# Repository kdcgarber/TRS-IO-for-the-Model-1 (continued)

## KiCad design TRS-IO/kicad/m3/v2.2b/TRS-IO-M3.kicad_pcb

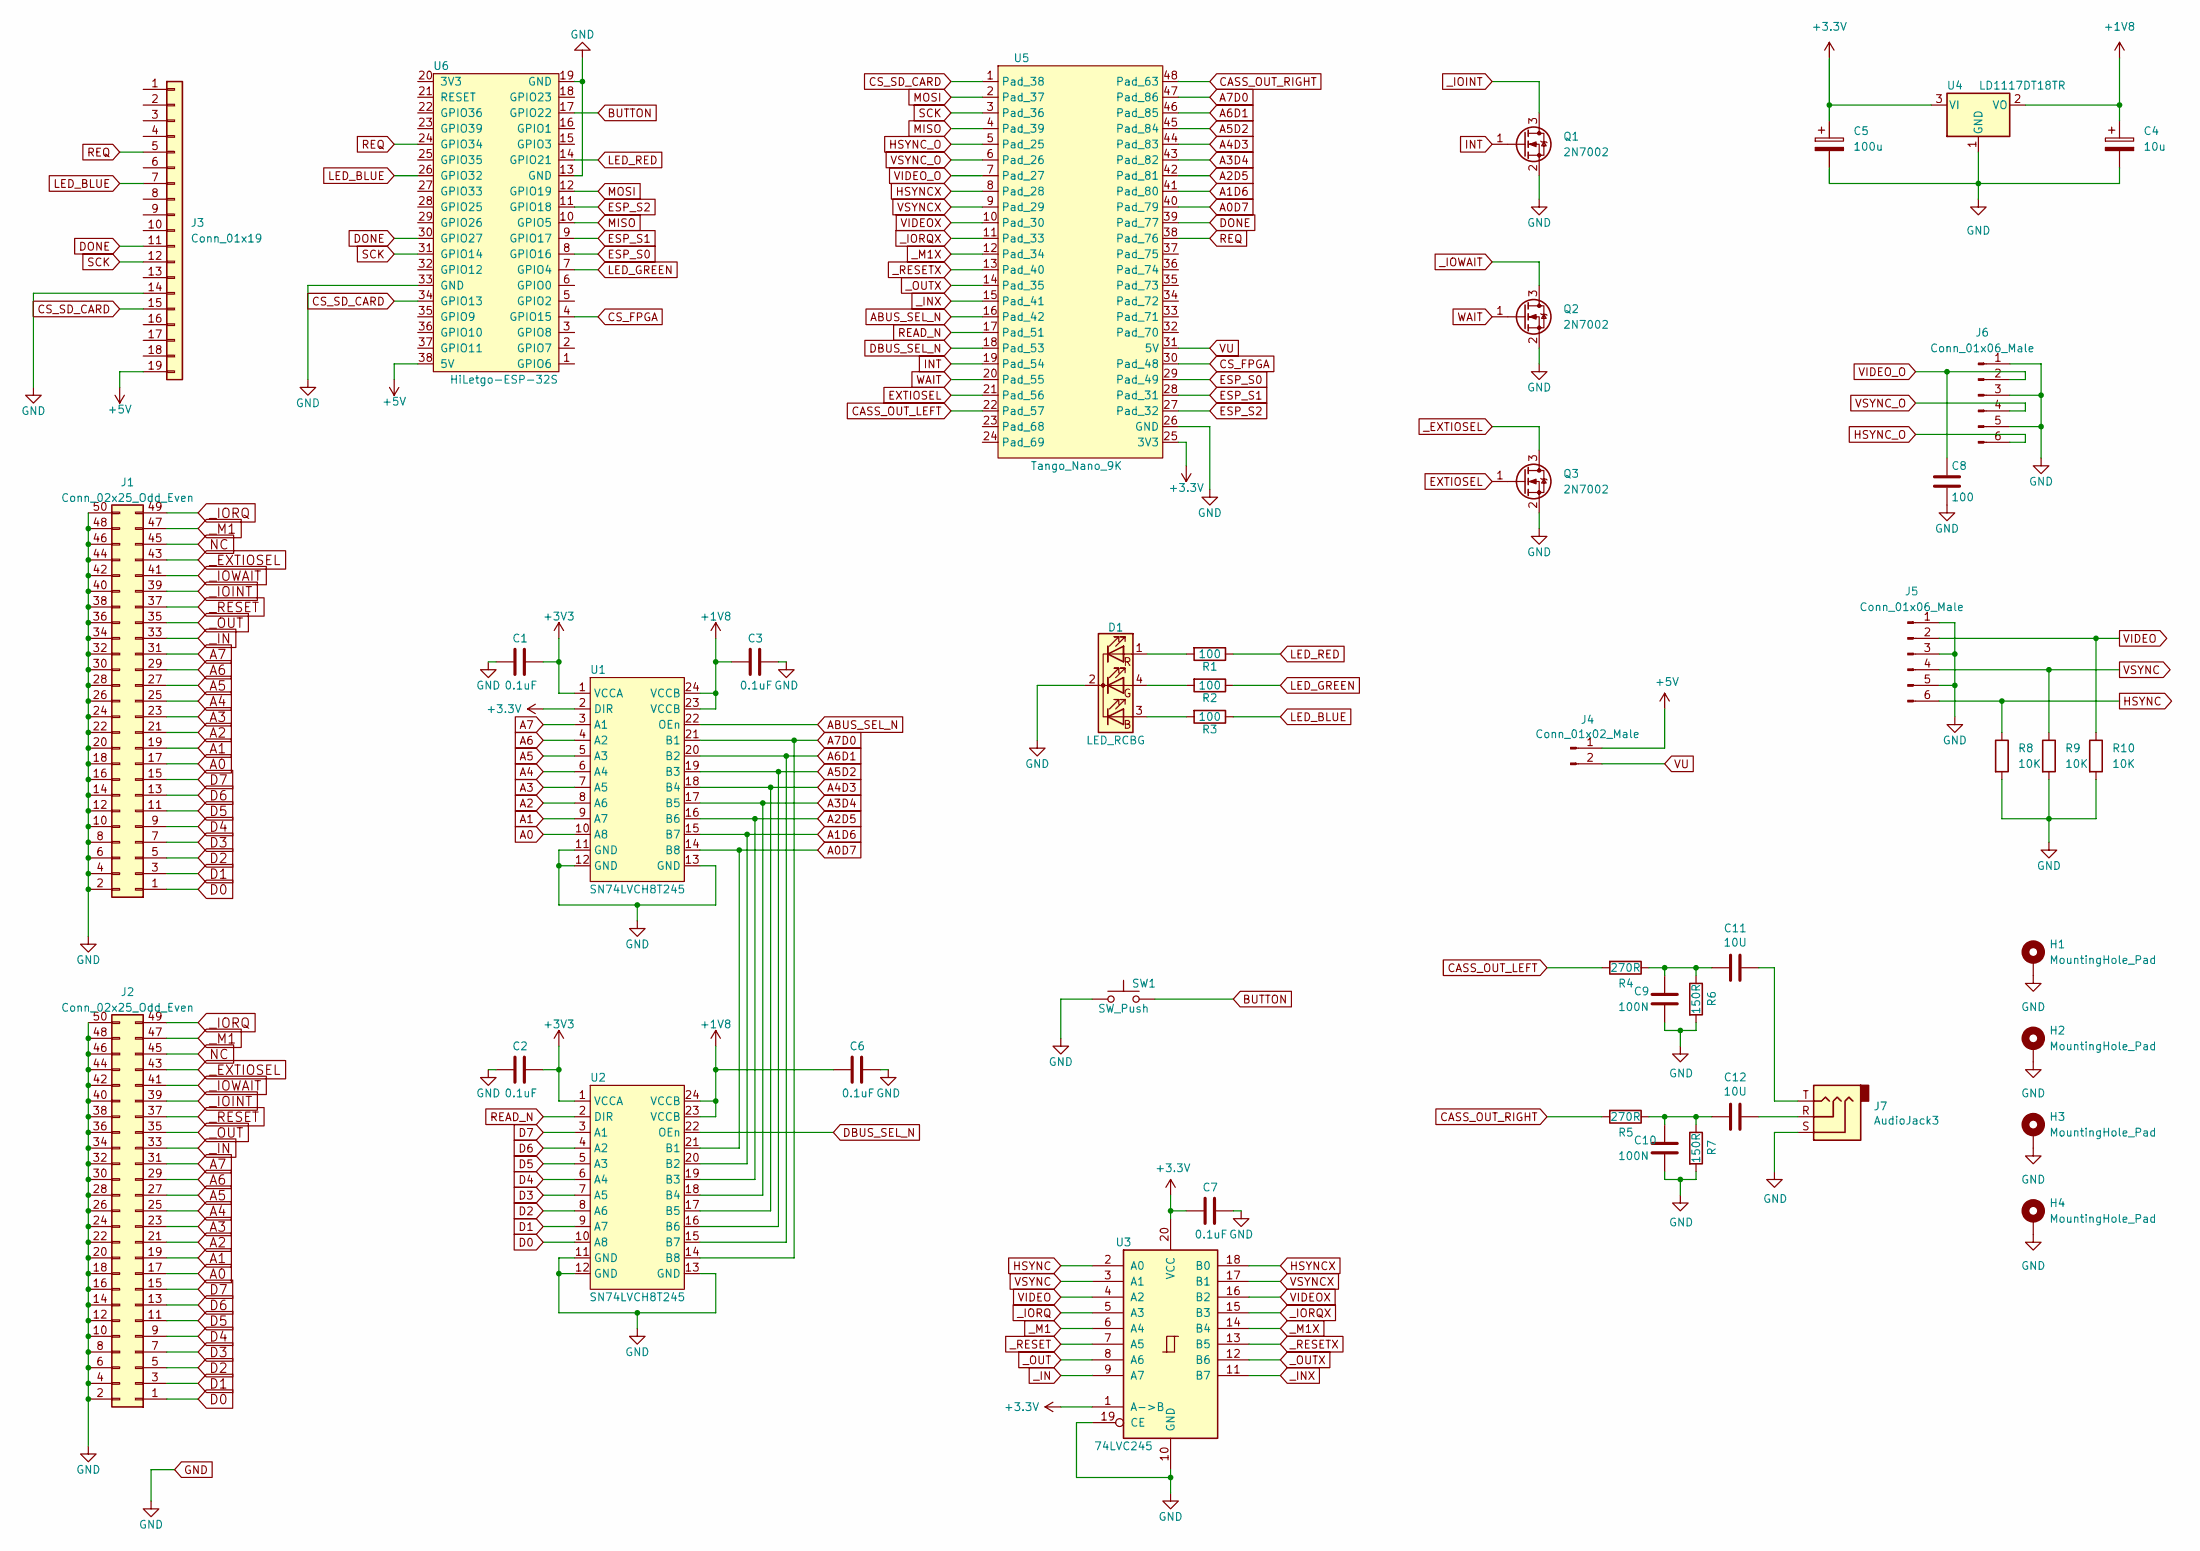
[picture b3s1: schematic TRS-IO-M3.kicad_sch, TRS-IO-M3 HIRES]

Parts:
C1, C2, C3, C6, C7: 0.1uF; C_0805_2012Metric_Pad1.18x1.45mm_HandSolder
C4: 10u; C_1206_3216Metric_Pad1.33x1.80mm_HandSolder
C5: 100u; C_1206_3216Metric_Pad1.33x1.80mm_HandSolder
C8: 100; C_0805_2012Metric_Pad1.18x1.45mm_HandSolder
C9, C10: 100N; C_0805_2012Metric_Pad1.18x1.45mm_HandSolder
C11, C12: 10U; C_1206_3216Metric_Pad1.33x1.80mm_HandSolder
D1: LED_RCBG; LED_D5.0mm-4_RGB
H1, H2, H3, H4: MountingHole_Pad; MountingHole_3mm_Pad_Via
J1: Conn_02x25_Odd_Even; EDGE50
J2: Conn_02x25_Odd_Even; Pin_Header_Straight_2x25_Pitch2.54mm
J3: Conn_01x19; PinHeader_1x19_P2.54mm_Vertical
J4: Conn_01x02_Male; PinHeader_1x02_P2.54mm_Vertical
J5, J6: Conn_01x06_Male; PinHeader_1x06_P2.54mm_Horizontal
J7: AudioJack3; Jack_3.5mm_CUI_SJ1-3535NG_Horizontal_CircularHoles
Q1, Q2, Q3: 2N7002; SOT-23
R1, R2, R3: 100; R_0805_2012Metric_Pad1.20x1.40mm_HandSolder
R4, R5: 270R; R_0805_2012Metric_Pad1.20x1.40mm_HandSolder
R6, R7: 150R; R_0805_2012Metric_Pad1.20x1.40mm_HandSolder
R8, R9, R10: 10K; R_0805_2012Metric_Pad1.20x1.40mm_HandSolder
SW1: SW_Push; SW_PUSH_6mm_H9.5mm
U1, U2: SN74LVCH8T245; TSSOP-24_4.4x7.8mm_P0.65mm
U3: 74LVC245; SSOP-20_5.3x7.2mm_P0.65mm_slim
U4: LD1117DT18TR; TO-252-3_TabPin2
U5: Tango_Nano_9K; DIP-48_W22.9mm
U6: HiLetgo-ESP-32S; DIP-38_W22.9mm

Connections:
+1V8: C3.2, C4.1, C6.2, U1.23 (VCCB), U1.24 (VCCB), U2.23 (VCCB), U2.24 (VCCB), U4.2 (VO)
+5V: J3.19, J4.1, U6.38 (5V)
A0: J1.17, J2.17, U1.10 (A8)
A0D7: U1.14 (B8), U2.21 (B1), U5.40 (Pad_79)
A1: J1.19, J2.19, U1.9 (A7)
A1D6: U1.15 (B7), U2.20 (B2), U5.41 (Pad_80)
A2: J1.21, J2.21, U1.8 (A6)
A2D5: U1.16 (B6), U2.19 (B3), U5.42 (Pad_81)
A3: J1.23, J2.23, U1.7 (A5)
A3D4: U1.17 (B5), U2.18 (B4), U5.43 (Pad_82)
A4: J1.25, J2.25, U1.6 (A4)
A4D3: U1.18 (B4), U2.17 (B5), U5.44 (Pad_83)
A5: J1.27, J2.27, U1.5 (A3)
A5D2: U1.19 (B3), U2.16 (B6), U5.45 (Pad_84)
A6: J1.29, J2.29, U1.4 (A2)
A6D1: U1.20 (B2), U2.15 (B7), U5.46 (Pad_85)
A7: J1.31, J2.31, U1.3 (A1)
A7D0: U1.21 (B1), U2.14 (B8), U5.47 (Pad_86)
ABUS_SEL_N: U1.22 (OEn), U5.16 (Pad_42)
BUTTON: SW1.2, U6.17 (GPIO22)
CASS_OUT_LEFT: R4.2, U5.22 (Pad_57)
CASS_OUT_RIGHT: R5.2, U5.48 (Pad_63)
CS_FPGA: U5.30 (Pad_48), U6.4 (GPIO15)
CS_SD_CARD: J3.15, U5.1 (Pad_38), U6.34 (GPIO13)
D0: J1.1, J2.1, U2.10 (A8)
D1: J1.3, J2.3, U2.9 (A7)
D2: J1.5, J2.5, U2.8 (A6)
D3: J1.7, J2.7, U2.7 (A5)
D4: J1.9, J2.9, U2.6 (A4)
D5: J1.11, J2.11, U2.5 (A3)
D6: J1.13, J2.13, U2.4 (A2)
D7: J1.15, J2.15, U2.3 (A1)
DBUS_SEL_N: U2.22 (OEn), U5.18 (Pad_53)
DONE: J3.11, U5.39 (Pad_77), U6.30 (GPIO27)
ESP_S0: U5.29 (Pad_49), U6.8 (GPIO16)
ESP_S1: U5.28 (Pad_31), U6.9 (GPIO17)
ESP_S2: U5.27 (Pad_32), U6.11 (GPIO18)
EXTIOSEL: Q3.1 (G), U5.21 (Pad_56)
GND: C1.2, C2.2, C3.1, C4.2, C5.2, C6.1, C7.1, C8.2, C9.2, C10.2, D1.2 (K), H1.1, H2.1, H3.1, H4.1, J1.2, J1.4, J1.6, J1.8, J1.10, J1.12, J1.14, J1.16, J1.18, J1.20, J1.22, J1.24, J1.26, J1.28, J1.30, J1.32, J1.34, J1.36, J1.38, J1.40, J1.42, J1.44, J1.46, J1.48, J1.50, J2.2, J2.4, J2.6, J2.8, J2.10, J2.12, J2.14, J2.16, J2.18, J2.20, J2.22, J2.24, J2.26, J2.28, J2.30, J2.32, J2.34, J2.36, J2.38, J2.40, J2.42, J2.44, J2.46, J2.48, J2.50, J3.14, J5.1, J5.3, J5.5, J6.1, J6.3, J6.5, J7.S, Q1.2 (S), Q2.2 (S), Q3.2 (S), R6.2, R7.2, R8.2, R9.2, R10.2, SW1.1, U1.11 (GND), U1.12 (GND), U1.13 (GND), U2.11 (GND), U2.12 (GND), U2.13 (GND), U3.10 (GND), U3.19 (CE), U4.1 (GND), U5.26 (GND), U6.13 (GND), U6.19 (GND), U6.33 (GND)
HSYNC: J5.6, R8.1, U3.2 (A0)
HSYNCX: U3.18 (B0), U5.8 (Pad_28)
HSYNC_O: J6.6, U5.5 (Pad_25)
INT: Q1.1 (G), U5.19 (Pad_54)
LED_BLUE: J3.7, R3.1, U6.26 (GPIO32)
LED_GREEN: R2.1, U6.7 (GPIO4)
LED_RED: R1.1, U6.14 (GPIO21)
MISO: U5.4 (Pad_39), U6.10 (GPIO5)
MOSI: U5.2 (Pad_37), U6.12 (GPIO19)
NC: J1.45, J2.45
unnamed: C10.1, C12.2, R5.1, R7.1
unnamed: C11.1, J7.T
unnamed: C9.1, C11.2, R4.1, R6.1
unnamed: C12.1, J7.R
unnamed: D1.1 (RA), R1.2
unnamed: D1.3 (BA), R3.2
unnamed: D1.4 (GA), R2.2
READ_N: U2.2 (DIR), U5.17 (Pad_51)
REQ: J3.5, U5.38 (Pad_76), U6.24 (GPIO34)
SCK: J3.12, U5.3 (Pad_36), U6.31 (GPIO14)
VIDEO: J5.2, R10.1, U3.4 (A2)
VIDEOX: U3.16 (B2), U5.10 (Pad_30)
VIDEO_O: C8.1, J6.2, U5.7 (Pad_27)
VSYNC: J5.4, R9.1, U3.3 (A1)
VSYNCX: U3.17 (B1), U5.9 (Pad_29)
VSYNC_O: J6.4, U5.6 (Pad_26)
VU: J4.2, U5.31 (5V)
WAIT: Q2.1 (G), U5.20 (Pad_55)
_EXTIOSEL: J1.43, J2.43, Q3.3 (D)
_IN: J1.33, J2.33, U3.9 (A7)
_INX: U3.11 (B7), U5.15 (Pad_41)
_IOINT: J1.39, J2.39, Q1.3 (D)
_IORQ: J1.49, J2.49, U3.5 (A3)
_IORQX: U3.15 (B3), U5.11 (Pad_33)
_IOWAIT: J1.41, J2.41, Q2.3 (D)
_M1: J1.47, J2.47, U3.6 (A4)
_M1X: U3.14 (B4), U5.12 (Pad_34)
_OUT: J1.35, J2.35, U3.8 (A6)
_OUTX: U3.12 (B6), U5.14 (Pad_35)
_RESET: J1.37, J2.37, U3.7 (A5)
_RESETX: U3.13 (B5), U5.13 (Pad_40)

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
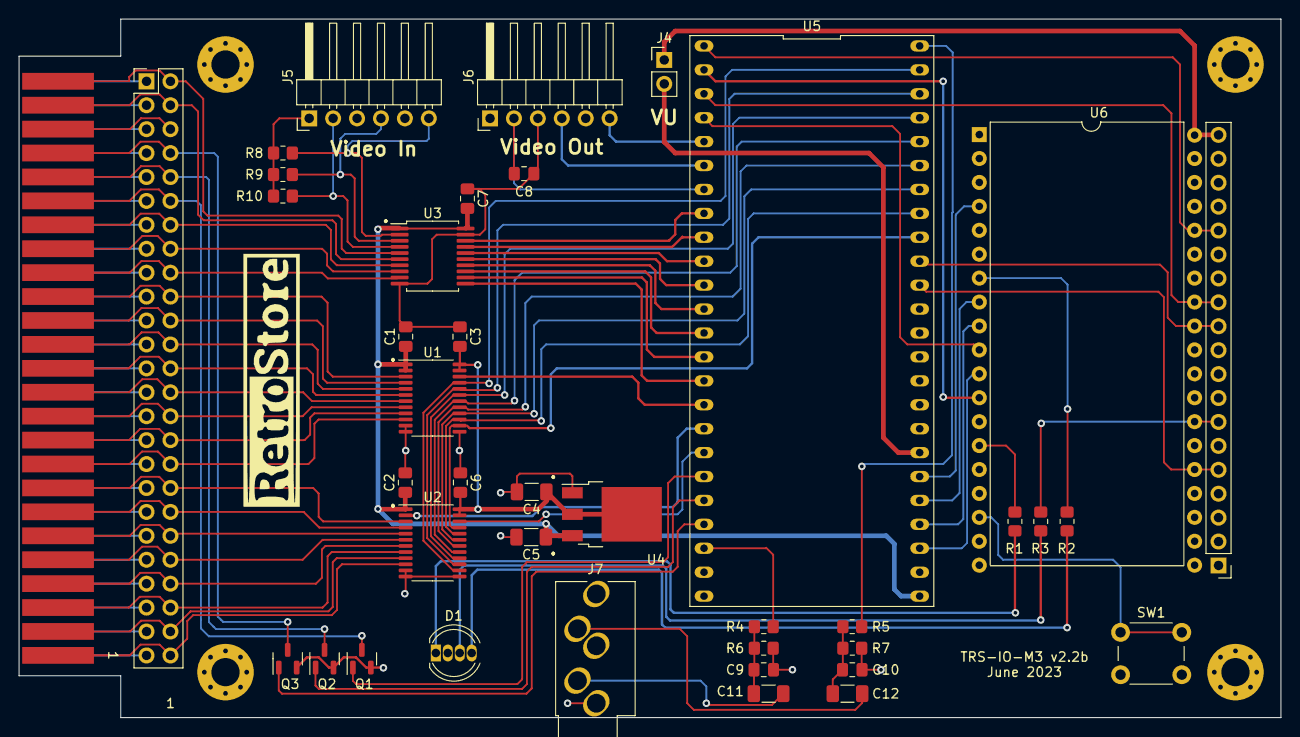
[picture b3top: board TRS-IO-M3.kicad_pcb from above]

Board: 2 copper layers, 134.0 x 74.2 mm, 45 parts (0 on the bottom side), 81 nets.

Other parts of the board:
G1: LOGO

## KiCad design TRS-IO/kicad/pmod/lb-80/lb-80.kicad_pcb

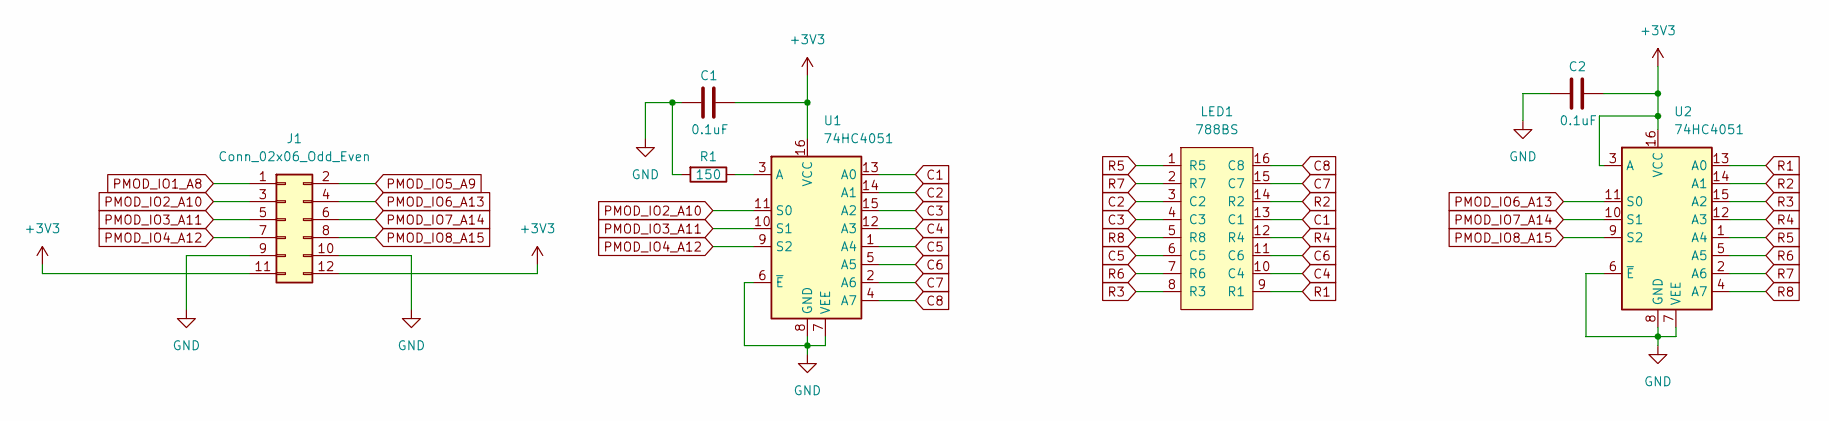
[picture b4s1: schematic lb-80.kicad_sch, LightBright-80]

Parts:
C1, C2: 0.1uF; C_0805_2012Metric_Pad1.18x1.45mm_HandSolder
J1: Conn_02x06_Odd_Even; PinSocket_2x06_P2.54mm_Vertical; LCSC C358728
LED1: 788BS
R1: 150; R_0805_2012Metric_Pad1.20x1.40mm_HandSolder
U1, U2: 74HC4051; TSSOP-16_4.4x5mm_P0.65mm; LCSC C352826

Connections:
+3V3: C1.1, C2.1, J1.11, J1.12, U1.16 (VCC), U2.3 (A), U2.16 (VCC)
C1: LED1.13 (C1), U1.13 (A0)
C2: LED1.3 (C2), U1.14 (A1)
C3: LED1.4 (C3), U1.15 (A2)
C4: LED1.10 (C4), U1.12 (A3)
C5: LED1.6 (C5), U1.1 (A4)
C6: LED1.11 (C6), U1.5 (A5)
C7: LED1.15 (C7), U1.2 (A6)
C8: LED1.16 (C8), U1.4 (A7)
GND: C1.2, C2.2, J1.9, J1.10, R1.2, U1.6 (~E), U1.7 (VEE), U1.8 (GND), U2.6 (~E), U2.7 (VEE), U2.8 (GND)
unnamed: R1.1, U1.3 (A)
PMOD_IO1_A8: J1.1
PMOD_IO2_A10: J1.3, U1.11 (S0)
PMOD_IO3_A11: J1.5, U1.10 (S1)
PMOD_IO4_A12: J1.7, U1.9 (S2)
PMOD_IO5_A9: J1.2
PMOD_IO6_A13: J1.4, U2.11 (S0)
PMOD_IO7_A14: J1.6, U2.10 (S1)
PMOD_IO8_A15: J1.8, U2.9 (S2)
R1: LED1.9 (R1), U2.13 (A0)
R2: LED1.14 (R2), U2.14 (A1)
R3: LED1.8 (R3), U2.15 (A2)
R4: LED1.12 (R4), U2.12 (A3)
R5: LED1.1 (R5), U2.1 (A4)
R6: LED1.7 (R6), U2.5 (A5)
R7: LED1.2 (R7), U2.2 (A6)
R8: LED1.5 (R8), U2.4 (A7)

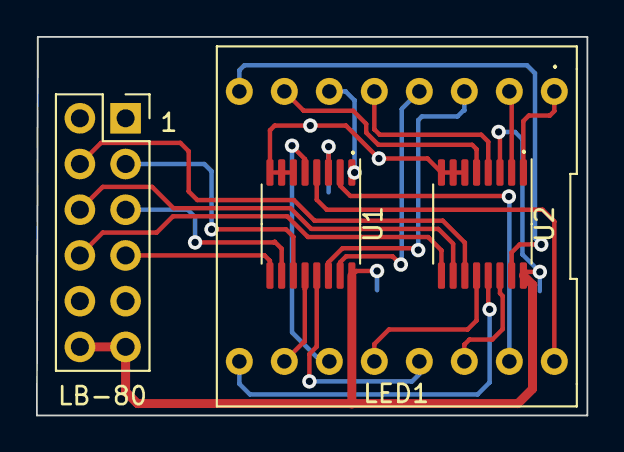
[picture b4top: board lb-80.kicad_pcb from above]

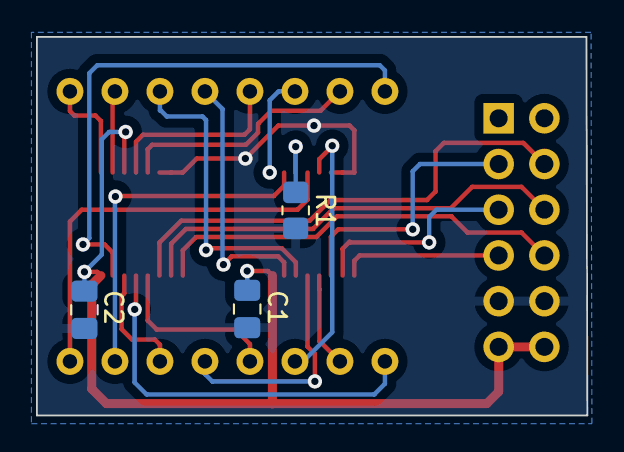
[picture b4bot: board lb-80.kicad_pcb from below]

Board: 2 copper layers, 30.6 x 21.0 mm, 7 parts (3 on the bottom side), 25 nets.

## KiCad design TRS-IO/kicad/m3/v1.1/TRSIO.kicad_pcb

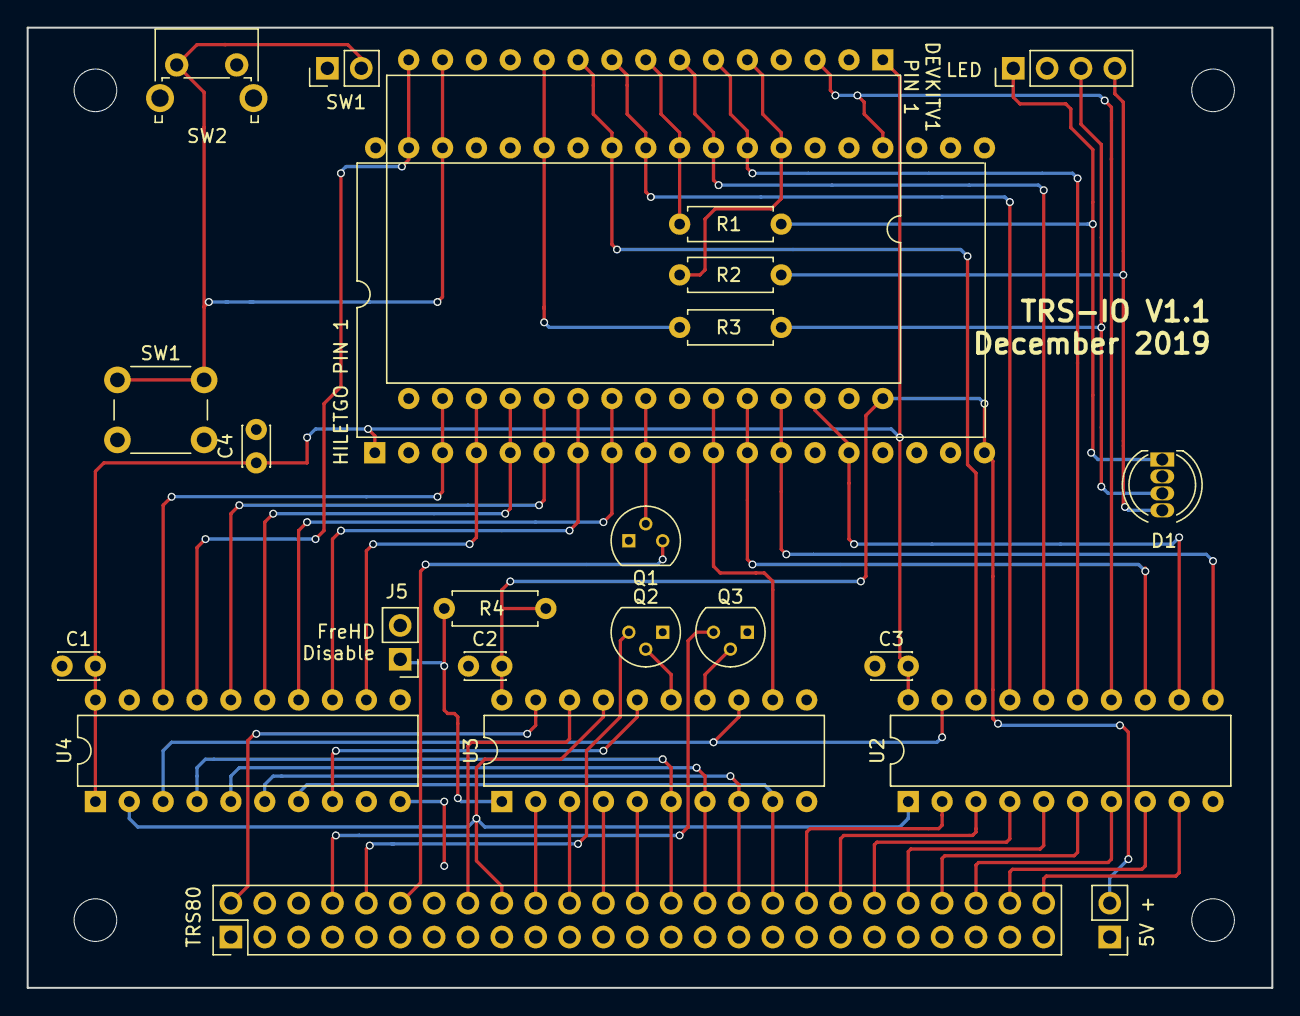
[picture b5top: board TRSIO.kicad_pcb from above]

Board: 2 copper layers, 93.3 x 72.0 mm, 24 parts (0 on the bottom side), 54 nets.

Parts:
C1, C2, C3, C4: 0.1; C_Disc_D3.0mm_W2.0mm_P2.50mm
D1: LED_RCBG; LED_D5.0mm-4
J1: TRS80; Pin_Header_Straight_2x25_Pitch2.54mm
J2: +5V; Pin_Header_Straight_1x02_Pitch2.54mm
J3: BUTTON; Pin_Header_Straight_1x02_Pitch2.54mm
J4: LED; Pin_Header_Straight_1x04_Pitch2.54mm
J5: FreHD Disable; Pin_Header_Straight_1x02_Pitch2.54mm
Q1, Q2, Q3: 2N7000; TO-92_Molded_Narrow
R1, R2, R3: 100; R_Axial_DIN0207_L6.3mm_D2.5mm_P7.62mm_Horizontal
R4: 4K7; R_Axial_DIN0207_L6.3mm_D2.5mm_P7.62mm_Horizontal
SW1: SW_Push; SW_PUSH_6mm_h9.5mm
SW2: Right Angle; SW_Tactile_SPST_Angled_PTS645Vx31-2LFS
U1A1: ESP32S; DIP-38_W22.9mm
U1B1: ESP32_AliExpress; DIP-30_W25.4mm
U2, U4: 74LVC245; DIP-20_W7.62mm
U3: GAL16V8; DIP-20_W7.62mm

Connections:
+3V3: C1.1, C3.1, C4.1, U1A1.1, U1B1.1, U2.20, U4.1, U4.20
+5V: C2.1, J2.2, R4.1, U1A1.19, U1B1.30, U3.20
//IORQ: J1.49, U3.19
//OUT: J1.35, U3.18
/A4: J1.25, U3.5
/A5: J1.27, U3.4
/A6: J1.29, U3.3
/A7: J1.31, U3.2
/D0: J1.1, U2.9
/D1: J1.3, U2.8
/D2: J1.5, U2.7
/D3: J1.7, U2.6
/D4: J1.9, U2.5
/D5: J1.11, U2.4
/D6: J1.13, U2.3
/D7: J1.15, U2.2
/ESP32_IN: U1A1.3, U1B1.17, U4.18
/ESP32_INT: Q1.2, U1A1.9, U1B1.23
/ESP32_P31: U1A1.4, U1B1.18, U4.12
/ESP32_SEL: U1A1.37, U1B1.15, U4.17
/ESP32_WAIT: U1A1.11, U1B1.25, U3.12
/ESP_EXTIOSEL: Q3.2, U3.14
/ESP_P31: U3.16, U4.8
/ESP_SEL: U2.19, U3.13, U4.3
/EXTIOSEL: J1.43, Q3.3
/IN: J1.33, U2.1, U3.17, U4.2
/IOINT: J1.39, Q1.3
/IOWAIT: J1.41, Q2.3
/WAIT: Q2.2, U3.15
/XHD: J5.1, R4.2, U3.1
A0: J1.17, U3.9, U4.7
A1: J1.19, U3.8, U4.6
A2: J1.21, U3.7, U4.5
A3: J1.23, U3.6, U4.4
BUTTON: J3.2, SW1.1, SW2.1, U1A1.36, U1B1.14
ESP32_A0: U1A1.7, U1B1.21, U4.13
ESP32_A1: U1A1.8, U1B1.22, U4.14
ESP32_A2: U1A1.5, U1B1.19, U4.15
ESP32_A3: U1A1.6, U1B1.20, U4.16
ESP32_D0: U1A1.13, U1B1.27, U2.11
ESP32_D1: U1A1.15, U1B1.28, U2.12
ESP32_D2: U1A1.12, U1B1.26, U2.13
ESP32_D3: U1A1.23, U1B1.3, U2.14
ESP32_D4: U1A1.27, U1B1.6, U2.15
ESP32_D5: U1A1.28, U1B1.7, U2.16
ESP32_D6: U1A1.30, U1B1.9, U2.17
ESP32_D7: U1A1.31, U1B1.10, U2.18
EXT_BLUE: D1.3, J4.3, R3.2
EXT_GREEN: D1.4, J4.4, R2.2
EXT_RED: D1.1, J4.1, R1.2
GND: C1.2, C2.2, C3.2, C4.2, D1.2, J1.2, J1.4, J1.6, J1.8, J1.10, J1.12, J1.14, J1.16, J1.18, J1.20, J1.22, J1.24, J1.26, J1.28, J1.30, J1.32, J1.34, J1.36, J1.38, J1.40, J1.42, J1.44, J1.46, J1.48, J1.50, J2.1, J3.1, J4.2, J5.2, Q1.1, Q2.1, Q3.1, SW1.2, SW2.2, U1A1.14, U1A1.32, U1A1.38, U1B1.2, U1B1.29, U2.10, U3.10, U4.9, U4.10, U4.19
LED_BLUE: R3.1, U1A1.33, U1B1.11
LED_GREEN: R2.1, U1A1.26, U1B1.5
LED_RED: R1.1, U1A1.29, U1B1.8

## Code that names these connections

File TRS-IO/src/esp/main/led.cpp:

#include "led.h"
#include "driver/gpio.h"
#include "freertos/FreeRTOS.h"
#include "freertos/task.h"
#include "freertos/event_groups.h"
#ifdef CONFIG_TRS_IO_PP
#include "spi.h"
#endif

#ifdef CONFIG_TRS_IO_MODEL_1
#define LED_RED 5
#define LED_GREEN 4
#define LED_BLUE 32
#else
#define LED_RED 21
#define LED_GREEN 32
#define LED_BLUE 4
#endif

#define LED_SEL_MASK ((1ULL << LED_RED) | (1ULL << LED_GREEN) | (1ULL << LED_BLUE))

#define BIT_R BIT0
#define BIT_G BIT1
#define BIT_B BIT2

#define BIT_BLINK BIT3
#define BIT_AUTO_OFF BIT4

#define BIT_TRIGGER BIT5

static TaskHandle_t task_handle;
static EventGroupHandle_t event_group;


#ifdef CONFIG_TRS_IO_TEST_LED
static void test_led()
{
  while(1) {
    // First blink twice in white
    set_led(true, true, true, false, false);
    vTaskDelay(500 / portTICK_PERIOD_MS);
    set_led(false, false, false, false, false);
    vTaskDelay(500 / portTICK_PERIOD_MS);
    set_led(true, true, true, false, false);
    vTaskDelay(500 / portTICK_PERIOD_MS);
    set_led(false, false, false, false, false);
    vTaskDelay(500 / portTICK_PERIOD_MS);

    // Red
    set_led(true, false, false, false, false);
    vTaskDelay(1000 / portTICK_PERIOD_MS);
    // Green
    set_led(false, true, false, false, false);
    vTaskDelay(1000 / portTICK_PERIOD_MS);
    // Blue
    set_led(false, false, true, false, false);
    vTaskDelay(1000 / portTICK_PERIOD_MS);
  }
}
#endif
    

static void led_task(void* p)
{
  TickType_t delay = portMAX_DELAY;
  uint32_t r = 0;
  uint32_t g = 0;
  uint32_t b = 0;
  bool on = false;
  bool auto_off = false;
  
  while(true) {
    EventBits_t bits = xEventGroupWaitBits(event_group,
                                           BIT_R | BIT_G | BIT_B |
                                           BIT_BLINK | BIT_AUTO_OFF |
                                           BIT_TRIGGER,
                                           pdTRUE, // Clear on exit
                                           pdFALSE, // Wait for all bits
                                           delay);
    if (bits != 0) {
      r = (bits & BIT_R) ? 1 : 0;
      g = (bits & BIT_G) ? 1 : 0;
      b = (bits & BIT_B) ? 1 : 0;
      delay = (bits & BIT_BLINK) ? 500 / portTICK_PERIOD_MS : portMAX_DELAY;
      auto_off = bits & BIT_AUTO_OFF;
      if (auto_off) {
        delay = 3000 / portTICK_PERIOD_MS;
      }
      on = true;
    }

    if (on) {
#ifdef CONFIG_TRS_IO_PP
      spi_set_led(r, g, b);
#else
      gpio_set_level((gpio_num_t) LED_RED, r);
      gpio_set_level((gpio_num_t) LED_GREEN, g);
      gpio_set_level((gpio_num_t) LED_BLUE, b);
#endif
    } else {
#ifdef CONFIG_TRS_IO_PP
      spi_set_led(0, 0, 0);
#else
      gpio_set_level((gpio_num_t) LED_RED, 0);
      gpio_set_level((gpio_num_t) LED_GREEN, 0);
      gpio_set_level((gpio_num_t) LED_BLUE, 0);
#endif
      if (auto_off) {
        delay = portMAX_DELAY;
      }
    }
    on = !on;
  }
}

void init_led()
{
#ifndef CONFIG_TRS_IO_PP
  gpio_config_t gpioConfig;

  // Configure LED
  gpioConfig.pin_bit_mask = LED_SEL_MASK;
  gpioConfig.mode = GPIO_MODE_OUTPUT;
  gpioConfig.intr_type = GPIO_INTR_DISABLE;
  gpio_config(&gpioConfig);
#endif

  event_group = xEventGroupCreate();
  xEventGroupClearBits(event_group, 0xff);
  xTaskCreatePinnedToCore(led_task, "led", 2048, NULL, 1, &task_handle, 0);
  
  // Turn LED off
  set_led(false, false, false, false, false);
#ifdef CONFIG_TRS_IO_TEST_LED
  test_led();
#endif
}
    

void set_led(bool r, bool g, bool b, bool blink, bool auto_off)
{
  EventBits_t mask = BIT_TRIGGER;

  if (r) {
    mask |= BIT_R;
  }
  if (g) {
    mask |= BIT_G;
  }
  if (b) {
    mask |= BIT_B;
  }
  if (blink) {
    mask |= BIT_BLINK;
  }
  if (auto_off) {
    mask |= BIT_AUTO_OFF;
  }
  xEventGroupSetBits(event_group, mask);
}

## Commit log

2025-07-04 First Push
2025-07-04 First Update
2025-07-05 Create LICENSE
